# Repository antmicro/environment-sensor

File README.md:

# Environment sensor board

Copyright (c) 2022-2024 [Antmicro](https://www.antmicro.com)

## Overview

This repository contains open hardware design files for an environment sensor board with temperature, pressure and humidity sensors. 

These sensors are placed on separated island in PCB corner, which can be easily broken out from the main board, and connected to it via provided connectors with a cable.

The design files were preapared in KiCad 7.x.

## Key features

* 50.00 mm X 26.50 mm PCB SIZE

* USB-C Connector for data and power

* STM32G474CET6 host MCU

* 128kB external FRAM 

* FTDI FT232r USB- UART converter

* SHT45 temperature + humidity sensor:
	* Typ. relative humidity accuracy ±1% RH
	* Operating relative humidity range 0 - 100% RH
	* Typ. temperature accuracy ±0.1 °C
	* Operating temperature range (-40) - (+125) °C
	
* BME280 temperature + humidity + pressure sensor:
	* Typ. relative humidity accuracy ±3% RH
	* Operating relative humidity range 10 - 100% RH
	* Typ. temperature accuracy ±1 °C
	* Operating temperature range (-40) - (+85) °C
	* Typ. pressure accuracy ±1 hPa
	* Operating pressure range 300 - 1100 hPa
	
* I2C connectors

* RTC battery backup

## Signal mapping

* FT232r:
	* JTAG on pins: DTR, RTS, DSR, DCD, CTS, RI (bitbang mode)
	
	* UART on pins: TXD, RXD

	* FTDI_USER_PB on CBUS0 (needs soldering R7)

* STM32G474CET6:
	* UART on PA2/PA3 pins

	* I2C on PA8/PA9/PA15(alt) or PB8/PB9(default) pins

	* FTDI_USER_PB on PC13 pin
	
	* FRAM_WP on PB11 pin

## I2C Address map (7-bit)
* FeRAM: 0x50 + A16(optional)
* SHT45: 0x44
* BME280: 0x76

## Test point assignment
* TP1 - JTAG NRST
* TP2 - JTAG TRST
* TP3 - JTAG JTMS
* TP4 - JTAG JTCK
* TP5 - JTAG TDO
* TP6 - JTAG TDI
* TP7 - FRAM Write Protect
* TP8 - MCU Boot Select
* TP9 - +3.3V power
* TP10 - GND
* TP11 - I2C SDA
* TP12 - I2C SCL 

## Repository structure

The main repository directory contains KiCad PCB project files, a LICENSE, and a README.
The remaining files are stored in the following directories:

* `img` - contains graphics for this README
* `doc` - containts board diagram

## Board diagram

## Licensing

This project is published under the [Apache-2.0](LICENSE) license.

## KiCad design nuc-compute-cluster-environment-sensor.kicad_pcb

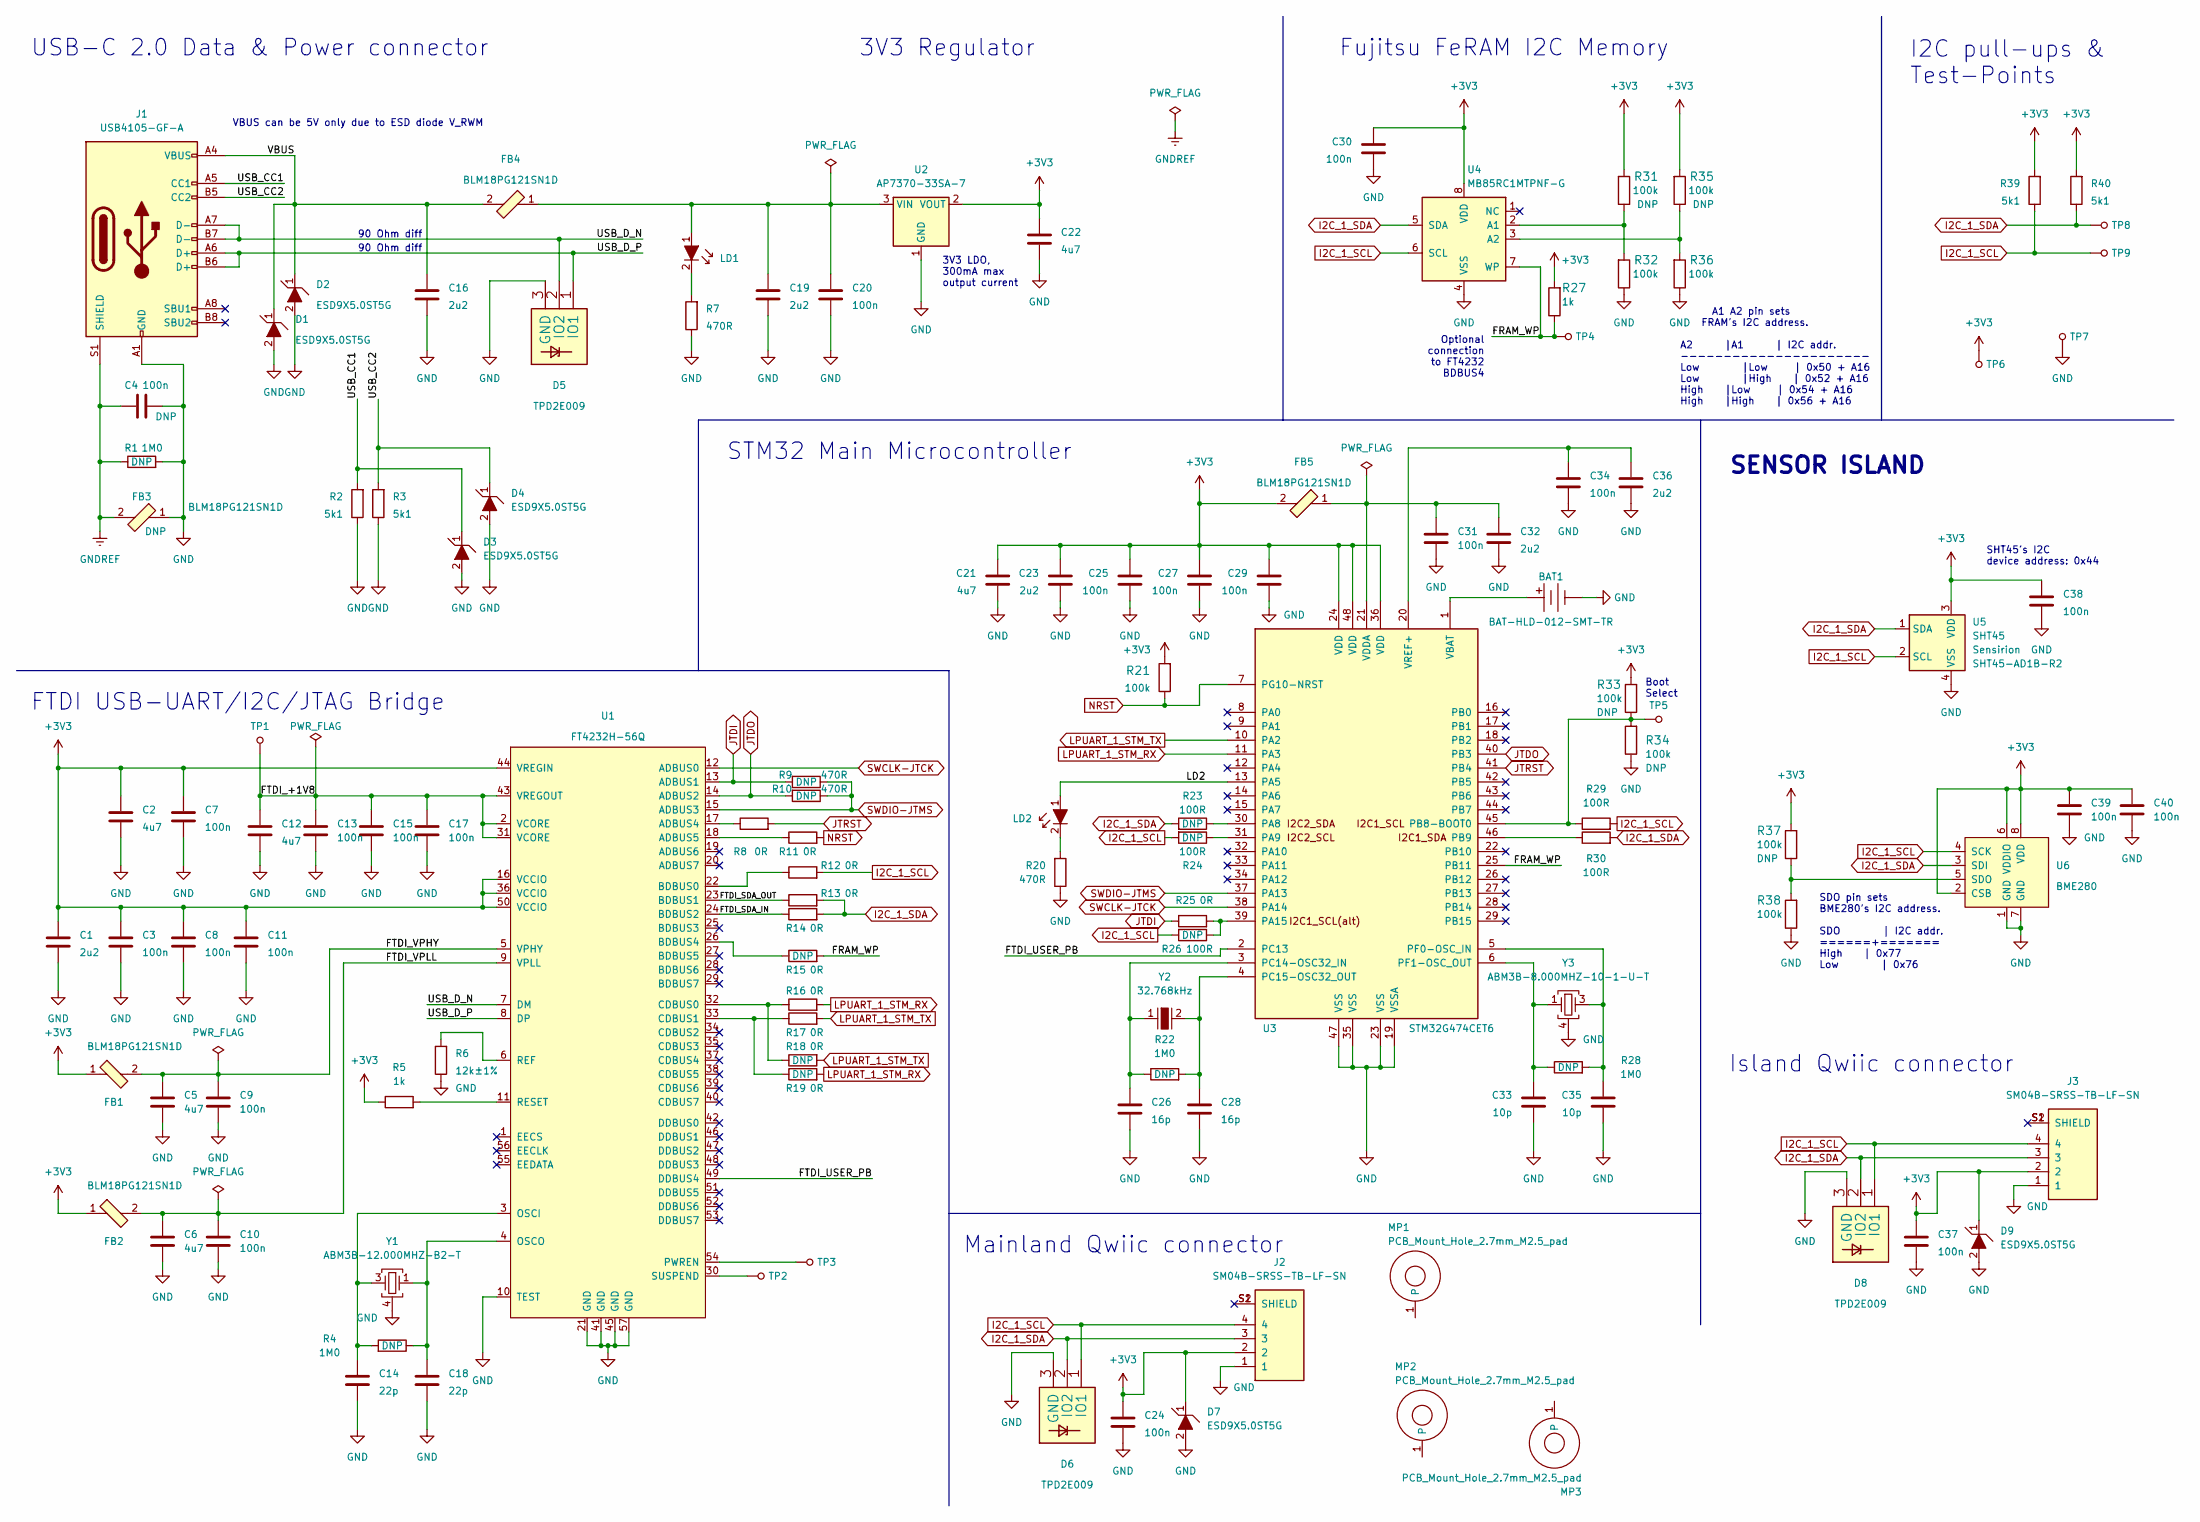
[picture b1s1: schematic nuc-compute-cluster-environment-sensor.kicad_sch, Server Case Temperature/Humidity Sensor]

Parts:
BAT1: BAT-HLD-012-SMT-TR; BAT_BAT-HLD-012-SMT-TR; MPN BAT-HLD-012-SMT-TR
C1, C16, C19, C23, C32, C36: C_2u2_0402; 0402-cap; MPN C1005X5R1A225K050BC
C2, C5, C6, C12, C21, C22: C_4u7_0402; 0402-cap; MPN GRM155R61A475MEAAD
C3, C4, C7, C8, C9, C10, C11, C13, C15, C17, C20, C24, C25, C27, C29, C30, C31, C34, C37, C38, C39, C40: C_100n_0402; 0402-cap; MPN GRM155R61H104KE14D
C14, C18: C_22p_0402; 0402-cap; MPN CC0402JRNPO9BN220
C26, C28: C_16p_0402; 0402-res; MPN 0402N160J500CT
C33, C35: C_10p_0402; 0402-cap; MPN MC0402N100D500CT
D1, D2, D3, D4, D7, D9: ESD9X5.0ST5G; SOD-923; MPN ESD9X5.0ST5G
D5, D6, D8: TPD2E009; SOT-723; MPN TPD2E009DRTR
FB1, FB2, FB3, FB4, FB5: BLM18PG121SN1D; 0603-res; MPN BLM18PG121SN1D
J1: USB4105-GF-A; GCT_USB4105-GF-A; MPN USB4105-GF-A
J2, J3: SM04B-SRSS-TB-LF-SN; MPN SM04B-SRSS-TB-LF-SN
LD1, LD2: LG_L29K-G2J1-24-Z; LED_0603; MPN KP-1608EC
MP1, MP2, MP3: PCB_Mount_Hole_2.7mm_M2.5_pad; mounting-hole-2.7mm-M2.5-Pad
R1, R4, R22, R28: R_1M0_0402; 0402-res; MPN CRG0402F1M0
R2, R3, R39, R40: R_5k1_0402; 0402-res; MPN SFR01MZPJ512
R5: R_1k_0402; 0402-res; MPN CR0402-FX-1001GLF
R6: R_12k_0402; 0402-res; Tolerance ±1%; MPN CRCW040212K0FKEDHP
R7, R9, R10, R20: R_470R_0402; 0402-res; MPN CRCW0402470RFKED
R8, R11, R12, R13, R14, R15, R16, R17, R18, R19, R25: R_0R_0402; 0402-res; MPN ERJ2GE0R00X
R21, R31, R32, R33, R34, R35, R36, R37, R38: R_100k_0402; 0402-res; MPN CRCW0402100KFKEDHP
R23, R24, R26, R29, R30: R_100R_0402; 0402-res; MPN CR0402-FX-1000GLF
R27: R_1k_0402; 0402-res; MPN CRCW04021K00FKEDHP
TP1, TP2, TP3, TP4, TP5, TP6, TP7, TP8, TP9: TP_SMD1MM; Testpoint_smd_1mm
U1: FT4232H-56Q; QFN-56-1EP_8x8mm_P0.5mm_EP5.5.9x5.9mm; MPN FT4232H-56Q-REEL
U2: AP7370-33SA-7; SOT-23-3; MPN AP7370-33SA-7
U3: STM32G474CET6; LQFP-48_B7x7mm_P0.5mm_0.20mmPadPadClearance_Pad0.30x1.20mm; MPN STM32G474CET6
U4: MB85RC1MTPNF-G; SOIC-8_W3.9mm; MPN MB85RC1MTPNF-G-JNERE1
U5: SHT45; Sensirion_DFN-4-1.5x1.5x0.5mm_P0.8mm; MPN SHT45-AD1B-R2
U6: BME280; Pressure_Sensor_LGA-8_2.5x2.5mm_BME280; MPN BME280
Y1: ABM3B-12.000MHZ-B2-T; ABM3B; MPN ABM3B-12.000MHZ-B2-T
Y2: ECS-_327-12_5-34B-TR; SMD-2_3.2x1.5mm; MPN ECS-.327-12.5-34B-TR
Y3: ABM3B-8.000MHZ-10-1-U-T; ABM3B; MPN ABM3B-8.000MHZ-10-1-U-T

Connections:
+3V3: C1.1, C2.1, C3.1, C7.1, C8.1, C11.1, C21.1, C22.1, C23.1, C24.2, C25.2, C27.2, C29.2, C30.2, C37.2, C38.2, C39.2, C40.2, D7.1, D9.1, FB1.1, FB2.1, FB5.2, J2.2, J3.2, R5.1, R21.2, R27.2, R31.2, R33.2, R35.2, R37.2, R39.2, R40.2, TP6.1, U1.16 (VCCIO), U1.36 (VCCIO), U1.44 (VREGIN), U1.50 (VCCIO), U2.2 (VOUT), U3.24 (VDD), U3.36 (VDD), U3.48 (VDD), U4.8 (VDD), U5.3 (VDD), U6.2 (CSB), U6.6 (VDDIO), U6.8 (VDD)
/FRAM_WP: R15.2, R27.1, TP4.1, U3.25 (PB11), U4.7 (WP)
/FTDI_+1V8: C12.1, C13.1, C15.1, C17.1, TP1.1, U1.2 (VCORE), U1.31 (VCORE), U1.43 (VREGOUT)
/FTDI_SDA_IN: R14.1, U1.24 (BDBUS2)
/FTDI_SDA_OUT: R13.1, U1.23 (BDBUS1)
/FTDI_USER_PB: U1.49 (DDBUS4), U3.2 (PC13)
/FTDI_VPHY: C5.1, C9.1, FB1.2, U1.5 (VPHY)
/FTDI_VPLL: C6.1, C10.1, FB2.2, U1.9 (VPLL)
/LD2: LD2.1, U3.13 (PA5)
/USB_CC1: D3.1, J1.A5 (CC1), R2.2
/USB_CC2: D4.1, J1.B5 (CC2), R3.2
/USB_D_N: D5.2 (IO2), J1.A7 (D-), J1.B7 (D-), U1.7 (DM)
/USB_D_P: D5.1 (IO1), J1.A6 (D+), J1.B6 (D+), U1.8 (DP)
/VBUS: C16.1, D1.1, D2.1, FB4.2, J1.A4 (VBUS), J1.A9 (VBUS), J1.B4 (VBUS), J1.B9 (VBUS)
GND: BAT1.N, C1.2, C2.2, C3.2, C4.2, C5.2, C6.2, C7.2, C8.2, C9.2, C10.2, C11.2, C12.2, C13.2, C14.1, C15.2, C16.2, C17.2, C18.1, C19.2, C20.2, C21.2, C22.2, C23.2, C24.1, C25.1, C26.1, C27.1, C28.1, C29.1, C30.1, C31.1, C32.2, C33.1, C34.1, C35.1, C36.2, C37.1, C38.1, C39.1, C40.1, D1.2, D2.2, D3.2, D4.2, D5.3 (GND), D6.3 (GND), D7.2, D8.3 (GND), D9.2, FB3.1, J1.A1 (GND), J1.A12 (GND), J1.B1 (GND), J1.B12 (GND), J2.1, J3.1, R1.2, R2.1, R3.1, R6.1, R7.1, R20.1, R32.1, R34.1, R36.1, R38.1, TP7.1, U1.10 (TEST), U1.21 (GND), U1.41 (GND), U1.45 (GND), U1.57 (GND), U2.1 (GND), U3.19 (VSSA), U3.23 (VSS), U3.35 (VSS), U3.47 (VSS), U4.4 (VSS), U5.4 (VSS), U6.1 (GND), U6.7 (GND), Y1.2, Y1.4, Y3.2, Y3.4
GNDREF: C4.1, FB3.2, J1.S1 (SHIELD), R1.1
I2C_1_SCL: D6.1 (IO1), D8.1 (IO1), J2.4, J3.4, R12.2, R24.2, R26.2, R29.2, R39.1, TP9.1, U4.6 (SCL), U5.2 (SCL), U6.4 (SCK)
I2C_1_SDA: D6.2 (IO2), D8.2 (IO2), J2.3, J3.3, R13.2, R14.2, R23.2, R30.2, R40.1, TP8.1, U4.5 (SDA), U5.1 (SDA), U6.3 (SDI)
JTDI: R9.2, R25.1, U1.13 (ADBUS1)
JTDO: R10.2, U1.14 (ADBUS2), U3.40 (PB3)
JTRST: R8.2, U3.41 (PB4)
LPUART_1_STM_RX: R16.2, R19.2, U3.11 (PA3)
LPUART_1_STM_TX: R17.2, R18.2, U3.10 (PA2)
NRST: R11.2, R21.1, U3.7 (PG10-NRST)
unnamed: BAT1.P, U3.1 (VBAT)
unnamed: C14.2, R4.2, U1.3 (OSCI), Y1.3
unnamed: C18.2, R4.1, U1.4 (OSCO), Y1.1
unnamed: C19.1, C20.1, FB4.1, LD1.1, U2.3 (VIN)
unnamed: C26.2, R22.1, U3.3 (PC14-OSC32_IN), Y2.1
unnamed: C28.2, R22.2, U3.4 (PC15-OSC32_OUT), Y2.2
unnamed: C31.2, C32.1, FB5.1, U3.21 (VDDA)
unnamed: C33.2, R28.1, U3.6 (PF1-OSC_OUT), Y3.1
unnamed: C34.2, C36.1, U3.20 (VREF+)
unnamed: C35.2, R28.2, U3.5 (PF0-OSC_IN), Y3.3
unnamed: LD1.2, R7.2
unnamed: LD2.2, R20.2
unnamed: R5.2, U1.11 (RESET)
unnamed: R6.2, U1.6 (REF)
unnamed: R8.1, U1.17 (ADBUS4)
unnamed: R11.1, U1.18 (ADBUS5)
unnamed: R12.1, U1.22 (BDBUS0)
unnamed: R15.1, U1.26 (BDBUS4)
unnamed: R16.1, R18.1, U1.32 (CDBUS0)
unnamed: R17.1, R19.1, U1.33 (CDBUS1)
unnamed: R23.1, U3.30 (PA8)
unnamed: R24.1, U3.31 (PA9)
unnamed: R25.2, R26.1, U3.39 (PA15)
unnamed: R29.1, R33.1, R34.2, TP5.1, U3.45 (PB8-BOOT0)
unnamed: R30.1, U3.46 (PB9)
unnamed: R31.1, R32.2, U4.2 (A1)
unnamed: R35.1, R36.2, U4.3 (A2)
unnamed: R37.1, R38.2, U6.5 (SDO)
unnamed: TP2.1, U1.30 (SUSPEND)
unnamed: TP3.1, U1.54 (PWREN)
SWCLK-JTCK: U1.12 (ADBUS0), U3.38 (PA14)
SWDIO-JTMS: R9.1, R10.1, U1.15 (ADBUS3), U3.37 (PA13)

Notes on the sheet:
3V3 LDO, 300mA max output current
Island Qwiic connector
FTDI USB-UART/I2C/JTAG Bridge
STM32 Main Microcontroller
3V3 Regulator
90 Ohm diff
USB-C 2.0 Data & Power connector
SDO pin sets BME280's I2C address. SDO | I2C addr. ======+======= High | 0x77 Low | 0x76
Optional connection to FT4232 BDBUS4
A1 A2 pin sets FRAM's I2C address. A2 |A1 | I2C addr. ---------------------- Low |Low | 0x50 + A16 Low |High | 0x52 + A16 High |Low | 0x54 + A16 High |High | 0x56 + A16
VBUS can be 5V only due to ESD diode V_RWM
Boot Select
I2C pull-ups & Test-Points
SENSOR ISLAND
SHT45's I2C device address: 0x44
Mainland Qwiic connector
Fujitsu FeRAM I2C Memory

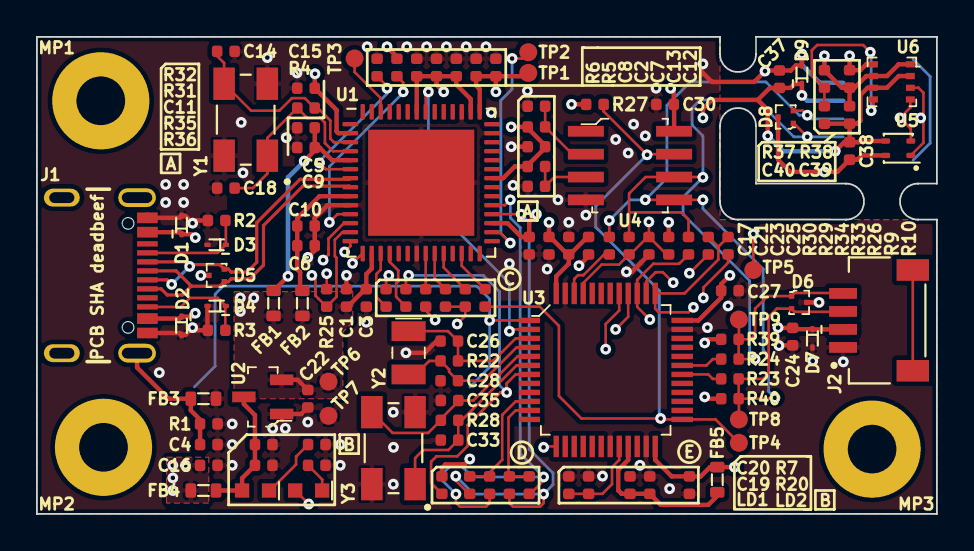
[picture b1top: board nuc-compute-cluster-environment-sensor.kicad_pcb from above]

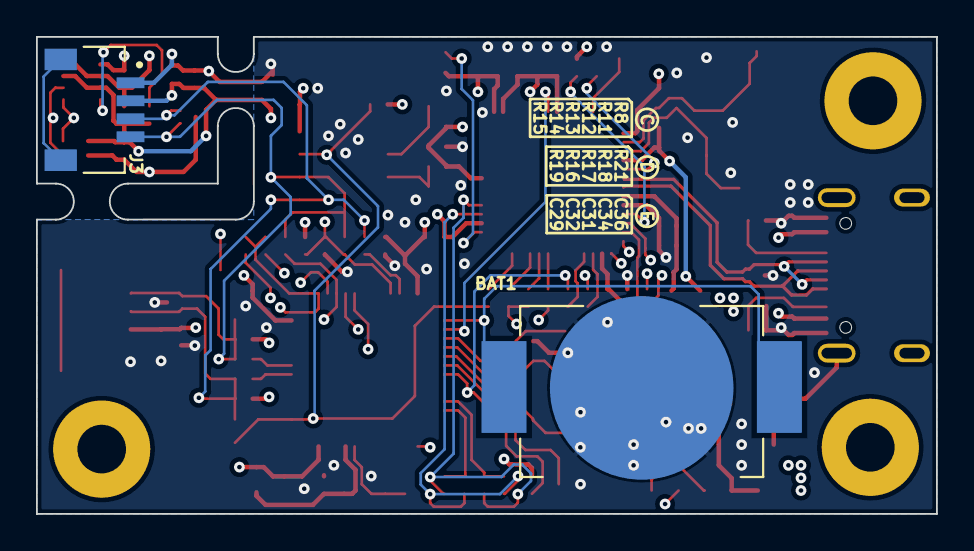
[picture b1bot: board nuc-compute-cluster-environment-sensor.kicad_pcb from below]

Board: 4 copper layers, 50.0 x 26.5 mm, 121 parts (2 on the bottom side), 56 nets.

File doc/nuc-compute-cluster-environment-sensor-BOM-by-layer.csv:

Reference,Quantity,Value,Footprint,Manufacturer,MPN,Layer,
C1 C9 C10,3,C_4u7_0402,C_0402_1005Metric,Murata,GRM155R61A475MEAAD,Top,
C14 C16,2,C_16p_0402,C_0402_1005Metric,Walsin,0402N160J500CT,Top,
C2 C3 C5 C6 C8 C12 C13 C15 C17 C18 C19 C22 C25 C26 C27 C28,16,C_100n_0402,C_0402_1005Metric,Murata,GRM155R61H104KE14D,Top,
C21 C23,2,C_10p_0402,C_0402_1005Metric,Murata,GCM1555C1H100GA16D,Top,
C4 C7 C11 C20 C24,5,C_2u2_0402,C_0402_1005Metric,TDK,C1005X5R1A225K050BC,Top,
D1 D2 D3 D4 D7 D9,6,ESD9X5.0ST5G,SOD-923,ON Semiconductor,ESD9X5.0ST5G,Top,
D5 D6 D8,3,TPD2E009_SOT-9X3,SOT-723,Texas Instruments,TPD2E009DRTR,Top,
FB1 FB2 FB3,3,FB_120Z_2A_0603,FB_0603_1608Metric,Murata,BLM18PG121SN1D,Top,
J1,1,USB-C_USB4105-GF-A,USB-C_GCT_USB4105-GF-A,GCT,USB4105-GF-A,Top,
J2,1,SM04B-SRSS-TB-LF-SN,SM04B-SRSS-TB-LF-SN,JST,SM04B-SRSS-TB(LF)(SN),Top,
LD1 LD2,2,LED_G_0603_KP-1608ZGC,LED_0603_1608Metric_G,Kingbright,KP-1608ZGC,Top,
MP1 MP2 MP3,3,PCB_Mount_Hole_2.7mm_M2.5_pad,mounting-hole-2.7mm-M2.5-Pad,,,Top,
R12 R17,2,R_470R_0402,R_0402_1005Metric,Bourns,CR0402-FX-4700GLF,Top,
R19 R24 R29 R30 R31 R32 R33 R34 R35 R36,10,R_100k_0402,R_0402_1005Metric,Bourns,CR0402-FX-1003GLF,Top,
R2 R26,2,R_1k_0402,R_0402_1005Metric,Bourns,CR0402-FX-1001GLF,Top,
R27 R28,2,R_100R_0402,R_0402_1005Metric,Bourns,CR0402-FX-1000GLF,Top,
R3 R4 R37 R38,4,R_5k1_0402,R_0402_1005Metric,Bourns,CR0402-FX-5101GLF,Top,
R5 R6 R7 R8 R9 R10 R13 R14 R20,9,R_0R_0402,R_0402_1005Metric,Panasonic,ERJ2GE0R00X,Top,
TP1 TP2 TP3 TP4 TP5 TP6,6,TP_1.5mm_SMD,TP_SMD_1.5mm,,,Top,
TP7 TP8 TP9 TP10 TP11 TP12,6,TP_1mm_SMD,Testpoint_smd_1mm,,,Top,
U1,1,FT232R_QFN,QFN-32-1EP_5x5mm,FTDI,FT232RQ-REEL,Top,
U2,1,AP7370-33SA-7,SOT-23-3,Diodes Incorporated,AP7370-33SA-7,Top,
U4,1,MB85RC1MTPNF-G,SOP-8_3.9x5.05mm_P1.27mm,Fujitsu Semiconductor,MB85RC1MTPNF-G-JNERE1,Top,
U5,1,SHT45,Sensirion_DFN-4-1.5x1.5x0.5mm_P0.8mm,Sensirion,SHT45-AD1B-R2,Top,
U6,1,BME280,Pressure_Sensor_LGA-8_2.5x2.5mm_BME280,Bosch Sensortec,BME280,Top,
Y1,1,ECS-_327-12_5-34B-TR,SMD-2_3.2x1.5mm,ECS Inc.,ECS-.327-12.5-34B-TR,Top,
Y2,1,ABM3B-8.000MHZ-10-1-U-T,ABM3B,Abracon,ABM3B-8.000MHZ-10-1-U-T,Top,
BAT1,1,BAT-HLD-012-SMT-TR,BAT_BAT-HLD-012-SMT-TR,Linx,BAT-HLD-012-SMT-TR,Bottom,
J3,1,SM04B-SRSS-TB-LF-SN,SM04B-SRSS-TB-LF-SN,JST,SM04B-SRSS-TB(LF)(SN),Bottom,
R1 R18 R25,3,R_1M_0402,R_0402_1005Metric,Bourns,CR0402-FX-1004GLF,DNP,
R11 R15 R16,3,R_0R_0402,R_0402_1005Metric,Panasonic,ERJ2GE0R00X,DNP,
R21 R22 R23,3,R_100R_0402,R_0402_1005Metric,Bourns,CR0402-FX-1000GLF,DNP,
#FLG01 #FLG02 #FLG03,3,PWR_FLAG,,,,Unknown,
#PWR01 #PWR033,2,GNDREF,,,,Unknown,
#PWR02 #PWR06 #PWR019,3,+5V,,,,Unknown,
#PWR025 #PWR030 #PWR034 #PWR036 #PWR044 #PWR047 #PWR049 #PWR054 #PWR056 #PWR059 #PWR061 #PWR064 #PWR066 #PWR068 #PWR072 #PWR073 #PWR077,17,+3V3,,,,Unknown,
#PWR03 #PWR04 #PWR05 #PWR07 #PWR08 #PWR09 #PWR010 #PWR011 #PWR012 #PWR013 #PWR014 #PWR015 #PWR016 #PWR017 #PWR018 #PWR020 #PWR021 #PWR022 #PWR023 #PWR024 #PWR026 #PWR027 #PWR028 #PWR029 #PWR031 #PWR032 #PWR035 #PWR037 #PWR038 #PWR039 #PWR040 #PWR041 #PWR042 #PWR043 #PWR045 #PWR046 #PWR048 #PWR050 #PWR051 #PWR052 #PWR053 #PWR055 #PWR057 #PWR058 #PWR060 #PWR062 #PWR063 #PWR065 #PWR067 #PWR069 #PWR070 #PWR071 #PWR074 #PWR075 #PWR076 #PWR078,56,GND,,,,Unknown,
U3,1,STM32G474CET6,LQFP-48_B7x7mm_P0.5mm_0.20mmPadPadClearance_Pad0.30x1.20mm,STMicroelectronics,STM32G474CET6,Unknown,

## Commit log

2022-11-23 [#39176] Create KiCad project, preliminary title block
2022-11-23 [#39176] Add .gitignore for KiCad designs, BOMs etc
2022-11-24 [#39176] SCH: Add USB-C input cicuitry, FT4232H-56Q, STM32G474Rx ICs
2022-11-25 [#39176] Added Fujitsu I²C 128KB FeRAM memory
2022-11-29 [#39176] Rename KiCad project to fit repository name
2022-12-08 [#39176] SCH: Add SHT45 & BME280 environment sensors
2022-12-08 [#39176] SCH: Add BS-7 CR2032 Battery Holder
2022-12-08 [#39176] SCH: Add SM04B-SRSS-TB-LF-SN QWIIC I²C expansion connector
2022-12-08 [#39176] SCH: Add 32kHz SMT Crystal Oscillator for Real-Time Clock
2022-12-09 [#39176] Change USB-C 2.0 connector to GCT USB4105-GF-A for easier manufacturability
2022-12-16 [#39832] SCH: Change MCU to STM32G474CET6
2022-12-16 [#39832] SCH: Add second QWIIC (SM04B-SRSS-TB-LF-SN) connector
2022-12-16 [#39832] SCH: Add extra 3V3 150mA LDO
2022-12-16 [#39832] SCH: Change battery holder to CR1216/CR1225 STM one
2022-12-23 [#39832] SCH: Wire up 32kHz RTC crystal to MCU
2022-12-23 [#39832] SCH: Add an DNP parallel 1M resistor to 32kHz RTC crystal for eventual oscillation stabilization
2022-12-23 [#39832] SCH: Add & wire up 8MH main MCU ceramic oscillator
2022-12-23 [#39832] SCH: Adjust 8MHz oscillator load capacitors
2022-12-23 [#39832] SCH: Complete circuitry near USB-C & 3V3 LDO, connect BAT to MCU
    Complete changelog:
    - Connect battery to MCU,
    - add more ESD protection to USB-C,
    - rearrange schematic,
    - increase filtering caps on USB-C input to 2x2u2,
    - change caps to 0402 where possible,
2022-12-23 [#39832] SCH: Add parallel 100n cap and 1M resistor to connect USB-C GND & Shield, as DNP for now
2022-12-23 [#39832] SCH: Wire up STM32 according to Default Zephyr Peripheral Mapping & datasheet, wire up SHT45 & more
    Default Zephyr Peripheral Mapping listed at:
    https://docs.zephyrproject.org/3.1.0/boards/arm/nucleo_g474re/doc/index.html#default-zephyr-peripheral-mapping
    Full changelog:
    - To STM32: Wire up VDD & VDDA, I2C_1, JTAG/SWD, LPUART_1, NRST as global labels
    - Add LD2 Zephyr User LED circuit to STM32
    - Add 100n decoupling capacitors
2022-12-23 [#39832] SCH: Wire up the two QWIIC connections, wire up BME280, create "Sensor Island" section
2022-12-23 [#39832] SCH: Begin wiring up FT4232H-56Q,
    Complete changelog:
    - Change some decoupling caps from 2u2 to 4u7 due to FTDI datasheet requirements
    - Wire up the FT4232H-56Q power, oscillator & some input pins
    - Add 12MHz ceramic oscillator with accompanying elements
    - Add a DNP ferrite bead inbetween USB-C GND and SHIELD
2022-12-23 [#39832] SCH: Finish wiring up FT4232H-56Q.
2022-12-23 [#39832] SCH: Add 12k pull-up STM32's NRST, just in case
2022-12-23 [#39832] Add initial completed schematic PDF
2022-12-27 [#39832] SCH: Add note informing about 3V3 LDO output current
2022-12-27 SCH: Update BME280 & SHT45 symbols to fix datasheet link
2022-12-27 SCH: Update 3V3 LDO symbol
2022-12-27 [#39832] SCH: Add 3V3 LDO Power Good testpoint, update remarks
2022-12-27 [#39832] SCH: Add ESD protection diodes for 3V3 pins in QWIIC connectors, change most pull-ups to 100k
2022-12-27 [#39832] SCH: Divide schematic into sections, add section titles
2022-12-27 [#39832] SCH: Fix typos in I2C labels
2022-12-27 [#39832] SCH: Add extra 3V3 and GND test-points
2022-12-27 [#39832] SCH: Add extra 100n cap to BME280 supply
2022-12-27 [#39832] SCH: Fix FT4232H I2C connection, move FRAM Write Protect to BDBUS4
2022-12-27 [#39832] SCH: Fix USB_CC - ESD protetction TVSes miswiring
2022-12-27 [#39832] SCH: Fix missing pin 20(VREF+) on STM32, add decoupling caps for it
2022-12-27 [#39832] SCH: Move I2C series protection resistors, add level setting DNP resistors onto PB8/BOOT0
    Full changelog:
    - Remove 100R series protection resistors from Qwiic connectors
    - Add a single pair of 100R series protection resistors to STM32's I2C pins
    - Add a DNP 100k pull-up & 100k pull-down for STM32's BOOT0 pin
    - Add a "Boot Select" text note to above setters
2022-12-27 [#39832] SCH: Add optional alternate I2C bus connections to STM32 thru DNP resistors
    Full changelog:
    - Add optional I2C_1_SCL connection on PA15 (JTDI)
    - Add optional I2C_1 bus connection on I2C2 output pair PA8 & PA9
2022-12-27 [#39832] SCH: Change address setting PU/PD resistors to 100k for BOM unification
2022-12-27 [#39832] SCH: Rearranged components on 3V3 LDO input, removed redundant 0R from there
2022-12-27 [#39832] SCH: Change I2C pull-ups to 5k1 for BOM unification & better I2C 400kHz mode support
2022-12-27 [#39832] SCH: Tidy up GND-SHIELD connection elements' text fields
2022-12-27 [#39832] SCH: Fix UART TX/RX swap, add 0Rs just in case
2022-12-27 [#39832] SCH: Replace LDO with AP7370-33SA-7 for 300mA max 3V3 bus current
2022-12-27 [#39832] SCH: Wire FRAM's Write Protect to unused PB11, mark unused STM32 pins with No-Connect flags.
2022-12-27 [#39832] SCH: Wire FTDI's DBUS4 to STM32's PC13 as Zephyr's default User_PB
2022-12-27 [#39832] SCH: Add I2C address notes for SHT45 & BME280
2022-12-27 [#39832] Annotate schematic.
2022-12-27 [#39832] SCH: Set revision to 1.0.0, update date & generate schematic PDF
2023-01-03 Finished schematic review, corrected decoupling caps, initial component placement done
2023-01-03 Started to route signals to closest passive components to seek for possible placement optimization
2023-01-04 Another iteration of component placements, initial routing of signals
2023-01-05 Added mounting holes and changed PCB size to 50x30mm
2023-01-05 New component placement, FTDI and related passive components moved to bottom layer
2023-01-05 Initial routing, island part, USB and I2C buses finished
2023-01-09 Routing completed
2023-01-09 New component placement after review, all components moved to top layer except battery and connector
2023-01-10 Routing finished
2023-01-10 Designators' placement finished, DRC performed with no issues found
2023-01-10 Added 1k pullup on FRAM write protection pin, 470R serial resistors added on SWDIO and SWCLK, keepout zones for GND added around USB
2023-01-10 Clearance on filled zones increased to 0,25mm, small tweaks added on layout
2023-01-10 Added board markings, Rev 1.0.1
2023-01-11 Final tweaks, removing vias from the logos
2023-01-11 Gerbers generated, README added
2023-01-11 Corrected MPN and values on schematic for C13 C15 C17
2023-01-11 Modified README.md
2023-01-12 Small tweaks on schematic comments and PCB silkscreen, exported wrl models, README finished
2023-01-31 Fixed connection of SWD/JTAG configuration resistors
2023-03-09 Add diagram
2023-03-09 Update diagram font color
2023-05-23 Raw symbol update
2023-05-23 Update USB-C section
2023-05-23 clean doc
2023-05-23 Update FeRAM nad I2C TP
2023-05-23 Update Bridge section
2023-05-23 Standarize R_1M0 Resistor
2023-05-23 Bridge section update
2023-05-23 Update STM section
2023-05-23 Standarize full schematic
2023-05-23 ERC Update
2023-05-23 Update Fujitsu symbol
2023-05-24 update footprint for MB85RC1MTPNF-G and PCB recover
2023-05-24 Preliminaty PCB correction
2023-05-24 Fix DRC Errors and reduce Warrnings from 240 to 160
2023-05-25 PCB fixes
2023-05-25 Update BAT-HLD-012-SMT-TR footprint
2023-05-25 Reduce DRC warrnings from 160 to 63
2023-05-25 Footprints updates
2023-05-25 Update BAT_BAT-HLD-012-SMT-TR footprint
2023-05-25 Fix MB85RC1MTPNF-G footprint
2023-05-25 Place designators
2023-05-26 Fixing path
2023-05-26 Fix gnd path
2023-05-26 Update margin of Y2
2023-06-07 Update schematic labels, alter schematic title
2023-06-07 Create .wrl after standarization
2023-06-12 Change rotation of U4
2023-06-12 Update .wrl file
2023-06-12 update .wrl and U4 3D model rotation
2023-06-29 [#46245] Turn off visibility 1A - FTDI Section
2023-06-29 [#46245] Turn off visibility 1A - STM32 Section
2023-06-29 [#46245] Return DNF Field for some resistores - FTDI Section
2023-06-29 [#46245] Return DNF Field for some resistores - STM32 Section
2023-06-29 [#46245] Change position of R20
2023-06-29 [#46245] Update component MB85RC1MTPNF-G from antmicro library - Scheamtic and PCB
2023-08-16 Remove redundant files for new revision
2023-08-16 Change FT4232 to FT232 (schematic)
2023-08-16 Remove redundant routes, move components
2023-08-17 Add test points
2023-08-17 Route signals
2023-08-17 Widen +5V signal Fix clearance (DRC warnings)
2023-08-17 Add keepout near sensor island Fix disconnected tracks
2023-08-17 Widen VBUS signal
2023-08-17 Improve readability
2023-08-17 Rename components
2023-08-17 Add OSHW logo Improve USB differential line Improve Antmicro logo Change test points to 1.5mm
2023-08-18 Change test points to 1.5mm
2023-08-18 Rearrange PCB design
2023-08-18 Add JTAG pinout
2023-08-18 Improve silkscreen layout
2023-08-18 Update footprint QFN-32-1EP_5x5mm Fix text clearance on bottom
2023-08-23 Add 0R resistors on JTAG Work in progress
2023-08-24 Readme file update for production branch
2023-08-24 [#48355] add bom files with initial sourcing
2023-08-24 generate BOM for 15pcs with manually changed FTDI mpn
2023-10-20 [#46245] Update component MB85RC1MTPNF-G from antmicro library - Schematic and PCB
2023-10-20 Introduce component standardization
2023-10-20 [#47270] Fixed ERC warnings
2023-10-20 [#47270] Fix silkscreen overlaps
2023-10-20 [#47270] Bump revision to 1.0.3
2023-11-02 Cleanup
2023-11-08 50957 Add GH assets
2023-11-10 Update project name in assets
2024-06-17 Unify component vendors
2024-06-17 [#60742] Replace J3 island qwiic connector
2024-06-17 [#60742] Replace J2 mainland qwiic connector
2024-06-17 [#60742] Update baterry connector
2024-06-17 Fix VBUS zone Improve I2C_1_SCL routing
2024-06-17 Improve B table
2024-06-17 [#60742] Replace USB C connector
2024-06-17 Fix DNP
2024-06-17 Improve silkscreen markings
2024-06-17 Remove overlapping via
2024-06-17 Fix Y2 value and update symbol Update BAT1 symbol Fix Y1 value
2024-06-17 Minor routing improvements
2024-06-17 Convert to kicad7
2024-06-17 Manually widen FT power routes
2024-06-17 Improve Antmicro logo
2024-06-17 Minor improvements Add GND and VBSU vias Reroute NRST Move BAT1 designator
2024-06-17 Add GND vias
2024-06-17 [#60742] Globlib
2024-06-17 [#60742] U3 replace STM32
2024-06-17 Change differential pair routing
2024-06-17 Add reference table Add test points' tags and hide designators
2024-06-17 [#60742] U1 Replace FT232RQ
2024-06-17 Add DRC exclusions Mark OSHW logo as 'Not in schematic'
2024-06-17 [#60742] SCH - update rev
2024-06-17 [#60742] Add license
2024-06-17 [#60742] Rename project files, cleanup
2024-06-17 [#60742] U4 replace FeRAM memory
2024-06-17 [#60742] DRC warnings - update footprints
2024-06-17 [#60742] Y1 replace 32k oscillator
2024-06-17 [#60742] Update README
2024-06-17 [#60742] Fixed SHA on PCB
2024-06-17 [#60742] ERC fix errors and warnings
2024-06-17 [#60742] DRC - fix errors
2024-06-17 [#60742 Update board render]
2024-06-17 [#60742] DRC warnings WIP
2024-06-17 [#60742] DRC warnings - changed min text height
2024-06-17 [#60742] Y2 replace 8M oscillator
2024-06-17 [#60742] DRC clean warnings
2024-06-17 [#60742] Update images
2024-06-17 [#60742] Add updated components
2024-06-17 [#60742] DRC fix errors and warnings
2024-06-17 Upload assets
2024-06-17 [#60742] U6 replace temperature sensor
2024-06-17 Add stackup.csv
2024-08-06 [#63104] Add ortho photo and refresh assets
2025-01-21 [#71729] Update open hardware portal assets
2025-05-20 [#77733] Update orthoT_photo pics

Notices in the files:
parts and their libraries:
Copyright (c) 2022 Antmicro  [Apache 2.0 License](https://www.apache.org/licenses/LICENSE-2.0)
License: Copyright (c) 2022 Antmicro  [Apache2 license](https://www.apache.org/licenses/LICENSE-2.0
Copyright (c) 2022 Antmicro  [Apache2 license](https://www.apache.org/licenses/LICENSE-2.0
